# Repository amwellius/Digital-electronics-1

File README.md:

# Digital-electronics-1

## LINKS
### Link to EDA PlayGround
[EDA PlayGroud](https://www.edaplayground.com/playgrounds/user/242729)
### Link to GitHub repository
[GitHub repository](https://github.com/amwellius/Digital-electronics-1)

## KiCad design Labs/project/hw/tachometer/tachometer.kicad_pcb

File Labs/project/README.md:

# DIGITAL ELECTRONICS 1
**2021**, Faculty of Electrical Engineering and Communication [FEKT](https://www.fekt.vut.cz/) <br/> 
 <br/>
**Title:** Project 2021 <br/>
**Topic:** 3. Console for bike with hall sensor, measuring and displaying speed, traveled distance and burnt calories <br/>
**Time Window:** 
   - *Start of Project*: *April 7*
   - *End of Project*:   *May 4* <br/>

**Supervisor:** **_doc. Ing. Tomáš Frýza, Ph.D._** <br/>
**Vivado Teachers:** **_doc. Ing. Tomáš Frýza, Ph.D._**, **_Ing. Stanislav Rozum_**

# 3. Console for bike with hall sensor, measuring and displaying speed, traveled distance and burnt calories

### Team members

- **Martin Kousal**, **ID=** *221063* <br/> 
[Link to GitHub project folder]( http://github.com/mkousal/Digital-electronics-1-Tachometer) <br/> 
- **Matej Ledvina**, **ID=** *221339* <br/> 
[Link to GitHub]( https://github.com/Ledvuk/Digital-electronics-1) <br/> 
- **Tomáš Kříčka**, **ID=**  *223283* <br/> 
[Link to GitHub]( https://github.com/TomasKricka) <br/> 
- **Samuel Košík**, **ID=** *221056* <br/>
[Link to GitHub]( https://github.com/amwellius/Digital-electronics-1)

### Project objectives

Our application uses two hall sensors for measuring speed, traveled distance, burnt calories and time (not by the hall sensor). <br/>
This data is shown on four 7segment displays (one part).
  - Calories counting
  - Total time
  - Total distance traveled
  - Trip distance traveled
  - Speed measuring <br/>

Modes can be selected by pressing buttons (see below). <br/>
One hall sensor is used for measuring speed and traveled distance. Another one is for calories counting. <br/>
Burnt calories will increase only by stepping the pedals, not by downhill riding!

## Hardware description

   ### Programming Board
   
   - Main programming board is **Arty A7-100T**. It has four Pmod connectors (16.), we have used all of them
   - Other buttons and LEDs are not used => See **Main Board**

   ### Main Board

   - [Schematic](http://github.com/mkousal/Digital-electronics-1-Tachometer/tree/main/files/tachometerBoard_schematic.pdf)
   - **Consists of:** three buttons, 7segment display, Pmod connectors, LED status and two connectors for Hall sensors
   - Board is made for direct connection to Arty A7 board. Three buttons are used to controlling the tachometer. LED at the top shows what value is now displayed at the display
   - Used seven segment display with middle double dot and dots for decimal is TDCG1050m - [datasheet](https://www.vishay.com/docs/83180/tdcx10x0m.pdf)

   ### Hall sensor board

   - [Schematic](http://github.com/mkousal/Digital-electronics-1-Tachometer/tree/main/files/encoderBoard_schematic.pdf)
   - Hall sensor board only consists of hall sensor and a few passive components that are described in datasheet and connector
   - You can screw it by using M3 screw to your bicycle
   - Used sensor is *MH253* - [datasheet](https://datasheet.lcsc.com/szlcsc/1811141821_MST-Magnesensor-Tech-MST-MH253ESO_C114369.pdf)

## VHDL modules description

### Buttons
#### `Button_int`:
   - This block reads the input from real world buttons and translates them to commands which will be sent to the state_machine controller. When buttons *up* or *down* are            pressed, the interface will enter a cooldown state when no additional button presses will be registered (to prevent jitter) after the cooldown passes, the interface will        send an *up* or *down* command out
   - If the *ok* button is pressed, the device enters the cooldown state, after which it will wait for a longer ammount of time. If no additional *ok* button press is                registered, the interface will send out an *startstop* command
   - If, however, the *ok* button would be pressed again, the interface will send out the *reset* command
### Traveled distance
#### `km_total`:
   - This block counts the travel distance and sends it out to the display. Every 100 m (meters) an pulse will appear on the `meters_i` which will add to the total count of up        to *999,9 km* 
   - When the **trip mode** is activated the block will count the trip time and send it to the display instead, the total time is being still counted in the background
   - *rst signal* will make the current displayed data reset to 0 
   - The enable signal will be present if the trip is not paused, on *pause* the trip data is not counted
   - This block automaticaly wipes previous trip data when the mode is turned on

This block also contains a **function** which converts the traveled distance from *binary integer* to *BCD code* to be displayed on the 4 digit 7 segment display.

### Main controling module
#### `state_machine`:
   - This is the main utility block of the device. It recives commands from the button interface and switches the outputs accordingly. Inputs `up_i` and `down_i` will cycle          through the 4 modes of the device and light up their status LED 
   - While in a mode the *data stream* from its block will be sent to be displayed on the segment display via the `data_o`, with added decimal point or double dot if needed 
   - While in a mode the *reset* and *ok* commands also aply for the selected block only. The *trip mode* is special, because it does not generate data on its own, when              activated, it will send a mode change command to all blocks which will now store and display data in an additional variable as well as keeping the total count going 
   - The status LED of trip will remain on as we cycle through the other modes until it is paused by the *startstop* button or turned off via the reset. At this point all trip        data will be reset from all blocks and the normal total data will be displayed

### Time mode
#### `total_time`:
   - This block acts as a stopwatch. When startstop is applied, it will *start* or *pause* the counting
   - *Reset* will reset the total time
   - When the *trip mode* is enabled, the stopwatch will automatically start counting the trip time and will reset before every trip is started 
 
 This block also contains a **function** which converts the total time from *binary integer* to *BCD code* to be displayed on the 4 digit 7 segment display.

### SENSOR <br/>
#### `sensor`:
   - This block is used to calculate actual speed and triggering pulse every 100 meters for counting travelled distance <br/>
   - Uses input from hall sensor mounted at the front wheel. Output one trigger signal every counted 100 meters and calculate actual real speed and set it to display output   

### 7 Segment Driver Module <br/>
   - This block consists of 4 smaller modules: 
      1. `CLOCK`
      2. `UP_DOWN_COUNTER`
      3. `DRIVER_4X7SEG`
      4. `DECODER_7SEG` <br/>
#### `CLOCK`:
   - Generates 100MHz clock
   - This periodic signal is used in module `UP_DOWN_COUNTER`, which reacts on rising edge of the signal <br/>
   - Originally uses 4ms for each segment
#### `UP_DOWN_COUNTER`:
   - According settings (g_CNT_WIDTH), counts as the edge of the clock signal rises <br/>
#### `DRIVER_4X7SEG`:
   - Main module, drives four 7segment displays. It is determinated by `CLOCK` and `UP_DOWN_COUNTER` <br/>
   - Process MUX uses above modules to set data_outputs to each 7segment display <br/>
   - Input is a 16bit unsigned (`b"xxxx xxxx xxxx xxxx"`)
#### `DECODER_7SEG`:
   This module is used for displaying data on 7segment display. If have more displays, MUX has to be used <br/>
   Both, common cathode and common anode can be used as well

### Calories Mode
#### `calories`:
   - This block calculates burned calories by measuring the time between each pedals rotations 
   - Rotation is captured by hall probe attached to pedal
   - The 100 MHz clock is used for counting time. Every 0.5s a number is increased, which recalculates the calories formula 
   - When signal from hall probe is not generating for 2s, the number that was increasing is stopped. The amount of burned calories is sent to display
   
## Testbenches and simulations
#### `Button_int`:
   - Shows states of `button_int` block
   - In order to save time and make the inner working of this device more clear, all simulated data has been sped up  

#### `km_total`:
   - Screenshot demos how the counting works
   - In order to save time and make the inner working of this device more clear, all simulated data has been sped up

#### `state_machine`:
   - Screenshot below represents testbench of main unit
   - In order to save time and make the inner working of this device more clear, all simulated data has been sped up 

#### `total_time`:
   - Funcionality of total time counting is shown by this signals
   - In order to save time and make the inner working of this device more clear, all simulated data has been sped up

#### `sensor`: <br/>
   - First waveform shows how the speed calculation works. Calculated speed is written to the `s_disp_o`, which is 16bit word and is here until the new value is calculated
   
   - Second waveform shows pulsing at the `s_trigger_o` every 50 sensor's tick, which is equal to the 100 meters in real distance

#### `CLOCK`: <br/>
   - Generates 100 MHz clock signal

#### `UP_DOWN_COUNTER`: <br/>
   - As internal values set, counts with edge of the clock
   - 0-31 states:
   
   - 0-31 states:
   
   - 0-4 states = This is used in our application
   - Four 7segment displays are controlled by this states

#### `DRIVER_4X7SEG`:
   - These screenshots show how the multiplexer works
   - `s_data` is the main 16bit data input
   - `s_hex` is the 4bit data output, which is used in `DECODER_7SEG`. This module decodes the 4bit data value and diplays it on a specific 7segment display
   - `s_dig_o` shows which one of four displays is being used. `b"0001"` means display on very right side
   - `s_seg_o` represents common cathode bits

   - This screenshot shows a real situation, when input data will be refreshed every one second (tachometer)
   - If data is not changed for a while, displays will use last data. This prevents from wrong/unwanted values
   
#### `DECODER_7SEG`:
   - Decodes 4bit signal to 7bit (7 segments (+ decimal dot and colon))

#### `calories`:
   - The simulation is in ratio 1s = 10ms
   - In wave form is display calories counting in both modes and amount of burned calories is sending to display

## TOP module description and simulations
   - TOP module represents the whole project
   - Final test schema can be seen below:
   
   - After having **main board** and **hall sensor board** done, software can be written into Arty A7 board. Generated bitstream is available [here](http://github.com/mkousal/Digital-electronics-1-Tachometer/tree/main/sw/tachometer/tachometer.runs/impl_1/top.bit). <br/>

## Video

Video presentation is available [here](https://youtu.be/21QbKaQYVqw).

## References

   ### Used materials:
   - Theoretical knowledge from Digital-Electronics-1 Labs, 2021 > [Link]( https://github.com/tomas-fryza/Digital-electronics-1/tree/master/Labs)
   - Labs from classes **DE1** 
   - DE1 Lecture PDF > [Link]( https://moodle.vutbr.cz/pluginfile.php/331523/mod_resource/content/3/DE1_lecture_part4_CZE.pdf)
   - [7 Segment Display]( https://docs.rs-online.com/6e0e/0900766b8130126b.pdf)
   - [Hall sensor](https://datasheet.lcsc.com/szlcsc/1811141821_MST-Magnesensor-Tech-MST-MH253ESO_C114369.pdf)
 
   ### Used programs and its links:
   - [Xilinx Vivado 2020]( https://www.xilinx.com/products/design-tools/vivado.html)
   - [VSCode]( https://code.visualstudio.com/)
   - [KiCad]( https://www.kicad.org/)
   - [EdaPlayGround]( https://www.edaplayground.com/)
   - [Vivado tutorials]( https://vhdlwhiz.com/basic-vhdl-tutorials/ )
   - [Tutorial from Xilinx]( https://www.xilinx.com/support/documentation/university/Vivado-Teaching/HDL-Design/2013x/Nexys4/Verilog/docs-pdf/Vivado_tutorial.pdf)
   - [Board Editor]( https://jamboard.google.com/)
   - [GitHub Desktop]( https://desktop.github.com/)
   - [Git Bash]( https://git-scm.com/download/win)
   
________________________________________________________________________________
©2021, VUT FEKT, Brno, Czech Republic <br/>
Kousal Martin, Ledvina Matej, Kříčka Tomáš, Košík Samuel <br/>
**For Educational Purposes Only!**

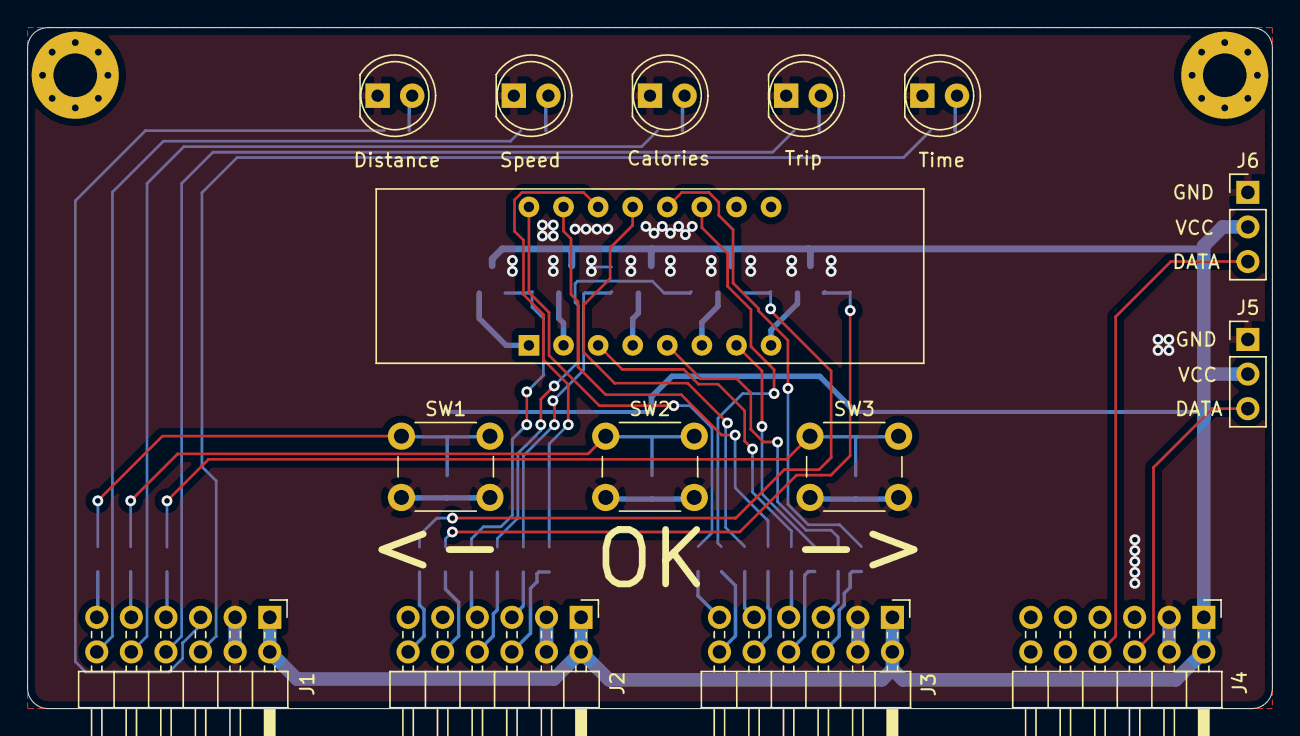
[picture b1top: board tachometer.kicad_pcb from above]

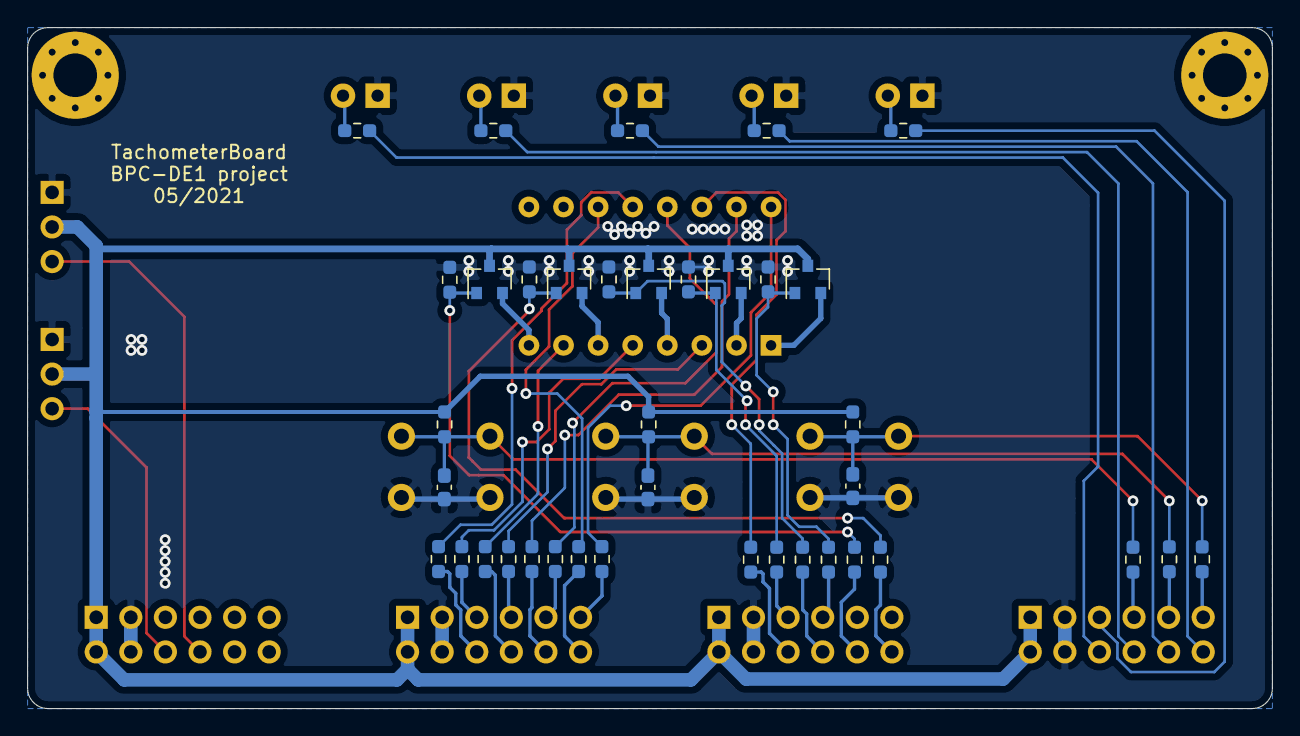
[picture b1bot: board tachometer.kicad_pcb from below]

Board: 2 copper layers, 91.4 x 50.0 mm, 53 parts (38 on the bottom side), 53 nets.

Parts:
C1, C2, C3: 100n; C_0603_1608Metric_Pad1.08x0.95mm_HandSolder
D1: TDCG1050m; TDCG10..m
D2, D3, D4, D5, D6: LED; LED_D5.0mm
J1: Pmod JA; PinHeader_2x06_P2.54mm_Horizontal
J2: Pmod JB; PinHeader_2x06_P2.54mm_Horizontal
J3: Pmod JC; PinHeader_2x06_P2.54mm_Horizontal
J4: Pmod JD; PinHeader_2x06_P2.54mm_Horizontal
J5: HallSensor1; PinHeader_1x03_P2.54mm_Vertical
J6: HallSensor2; PinHeader_1x03_P2.54mm_Vertical
Q1, Q2, Q3, Q4, Q5: BC817; SOT-23
R1, R12, R13, R15, R16, R18, R22, R27: 10k; R_0603_1608Metric_Pad0.98x0.95mm_HandSolder
R2, R3, R4, R5, R6, R7, R8, R9, R10, R19, R20, R23, R24, R25, R30, R31, R32: 220; R_0603_1608Metric_Pad0.98x0.95mm_HandSolder
R11, R14, R17, R21, R26: 1k5; R_0603_1608Metric_Pad0.98x0.95mm_HandSolder
SW1, SW2, SW3: SW_Push_Dual; SW_PUSH_6mm

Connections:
A11: J1.7, R32.2
A18: J1.8, R24.1
B11: J1.9, R31.2
B18: J1.10, R23.1
C15: J2.5, R14.2
D12: J1.5, R19.1
D13: J1.12, R20.1
D15: J2.7, R11.2
G2: J4.6, J5.3
G13: J1.11, R30.2
GND: C1.1, C2.1, C3.1, D2.1, D3.1, D4.1, D5.1, D6.1, J1.3, J1.4, J2.3, J2.4, J3.3, J3.4, J4.3, J4.4, J5.1, J6.1, R12.1, R15.1, R18.1, R22.1, R27.1, SW1.2, SW2.2, SW3.2
H2: J4.8, J6.3
J15: J2.6, R2.2
J17: J2.12, R17.2
J18: J2.10, R21.2
K15: J2.8, R26.2
K16: J1.6, R25.1
unnamed: C1.2, R1.2, R30.1, SW1.1
unnamed: C2.2, R13.2, R31.1, SW2.1
unnamed: C3.2, R16.2, R32.1, SW3.1
unnamed: D1.3, R5.1
unnamed: D1.5, R6.1
unnamed: D1.7, R9.1
unnamed: D1.11, R7.1
unnamed: D1.12, R10.1
unnamed: D1.13, R4.1
unnamed: D1.14, R2.1
unnamed: D1.15, R8.1
unnamed: D1.16, R3.1
unnamed: D2.2, R19.2
unnamed: D3.2, R20.2
unnamed: D4.2, R23.2
unnamed: D5.2, R24.2
unnamed: D6.2, R25.2
unnamed: Q1.1, R11.1, R12.2
unnamed: Q2.1, R14.1, R15.2
unnamed: Q3.1, R17.1, R18.2
unnamed: Q4.1, R21.1, R22.2
unnamed: Q5.1, R26.1, R27.2
SEG_1: D1.1, Q1.2
SEG_2: D1.2, Q2.2
SEG_3: D1.6, Q3.2
SEG_4: D1.8, Q4.2
SEG_5: D1.4, Q5.2
T13: J3.8, R9.2
U12: J3.11, R3.2
U13: J3.6, R10.2
U14: J3.12, R7.2
V10: J3.7, R5.2
V11: J3.5, R6.2
V12: J3.9, R4.2
V14: J3.10, R8.2
VCC: J1.1, J1.2, J2.1, J2.2, J3.1, J3.2, J4.1, J4.2, J5.2, J6.2, Q1.3, Q2.3, Q3.3, Q4.3, Q5.3, R1.1, R13.1, R16.1

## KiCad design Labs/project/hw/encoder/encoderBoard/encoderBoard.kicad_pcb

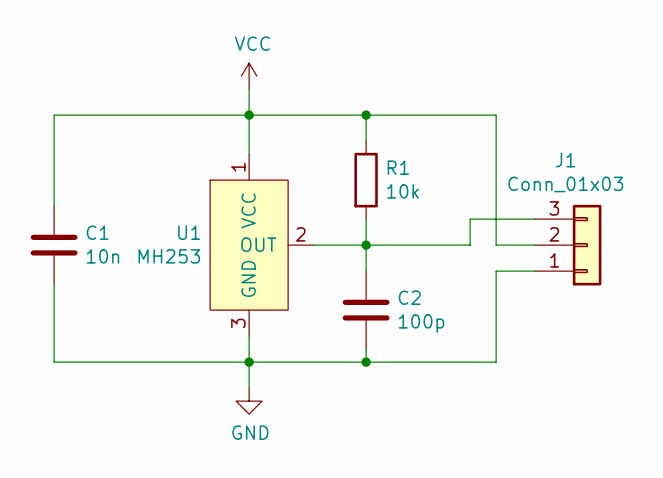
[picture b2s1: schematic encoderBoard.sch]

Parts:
C1: 10n; C_0402_1005Metric
C2: 100p; C_0402_1005Metric
J1: Conn_01x03; PinHeader_1x03_P2.54mm_Horizontal
R1: 10k; R_0402_1005Metric
U1: MH253; SOT-23

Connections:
GND: C1.2, C2.2, J1.1, U1.3 (GND)
unnamed: C2.1, J1.3, R1.2, U1.2 (OUT)
VCC: C1.1, J1.2, R1.1, U1.1 (VCC)

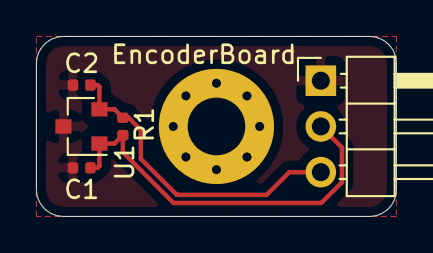
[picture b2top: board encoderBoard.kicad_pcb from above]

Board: 2 copper layers, 20.0 x 10.0 mm, 5 parts (0 on the bottom side), 3 nets.

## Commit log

2021-02-10 Vypracoval som bod 1
2021-02-12 added images
2021-02-12 added image
2021-02-12 added the last files
2021-02-17 Create 02-logic
2021-02-17 Create README.md
    02-logic
2021-02-17 screens
2021-02-24 lab 3 final
2021-02-24 03 start
2021-02-24 03 middle
2021-02-24 03 screens
2021-02-24 03 final
2021-03-03 lab4
2021-03-03 la4fin
2021-03-03 lab4final
2021-03-03 vivado files
2021-03-11 final 5
2021-03-17 create lab6
2021-03-17 lab6
2021-03-17 lab6 vivado files
2021-03-27 lab7 imgs
2021-03-31 lab8 readme
2021-03-31 imgs
2021-03-31 lab8 vivado files
2021-04-03 smart trafic update
2021-04-03 lab8 vivado
2021-04-27 readme_test
2021-04-29 images
2021-05-03 final project files
2021-05-04 final
